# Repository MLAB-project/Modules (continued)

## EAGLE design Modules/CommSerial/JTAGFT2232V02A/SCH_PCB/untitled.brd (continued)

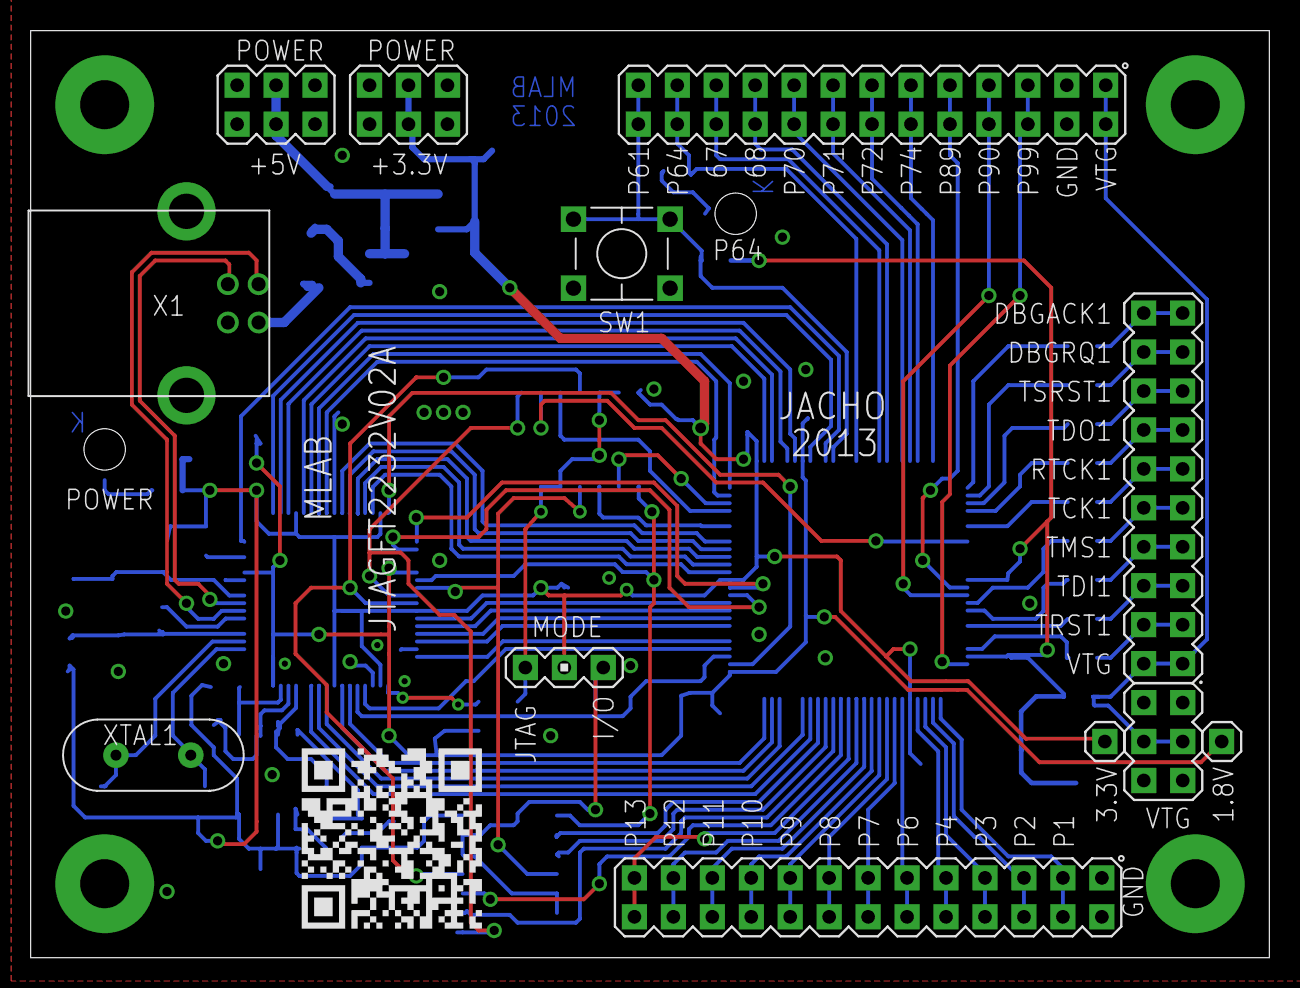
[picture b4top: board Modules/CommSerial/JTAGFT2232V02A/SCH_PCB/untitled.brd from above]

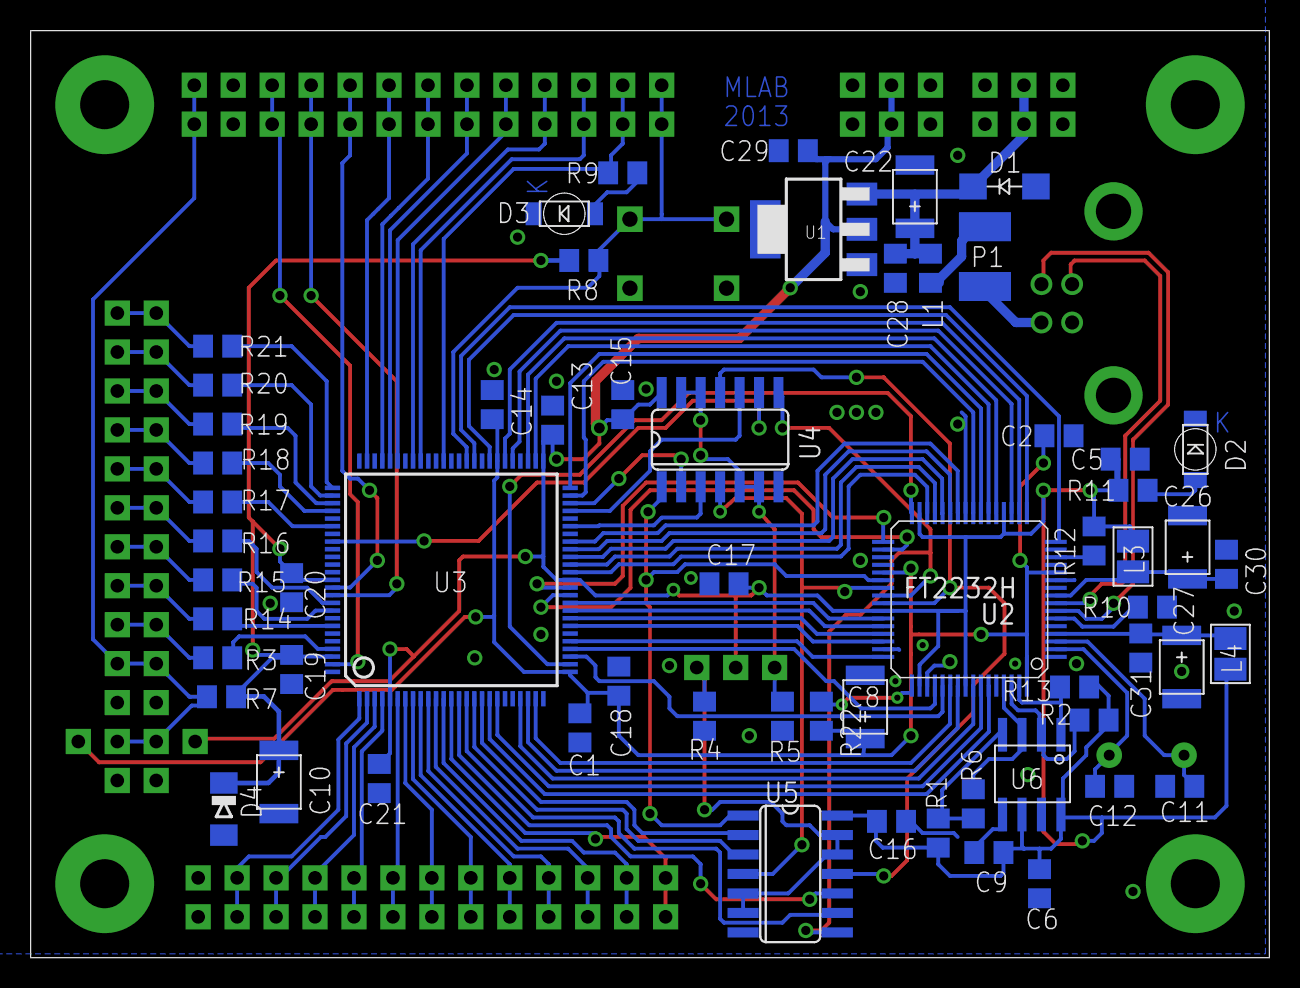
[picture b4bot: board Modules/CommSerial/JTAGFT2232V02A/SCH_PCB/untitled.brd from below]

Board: 2 copper layers, 80.8 x 60.5 mm, 77 parts (61 on the bottom side), 106 nets.

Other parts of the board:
SV9: MA01-1

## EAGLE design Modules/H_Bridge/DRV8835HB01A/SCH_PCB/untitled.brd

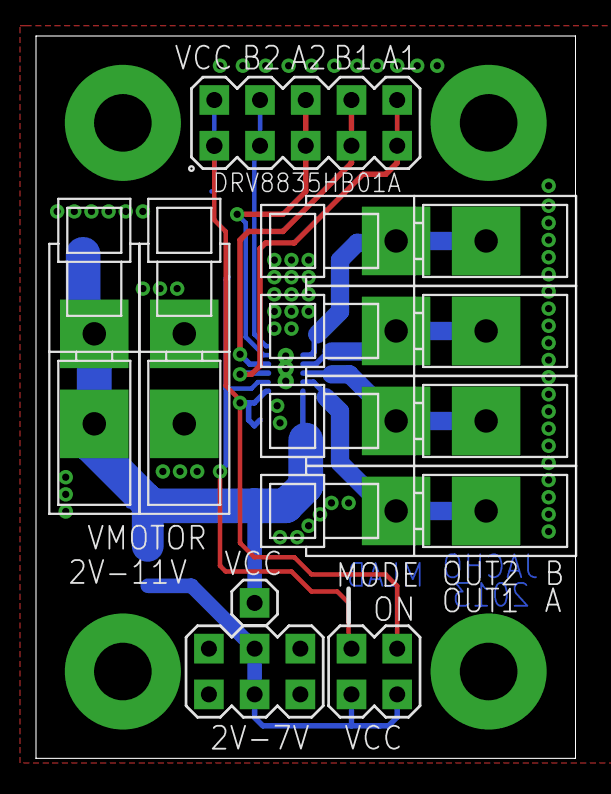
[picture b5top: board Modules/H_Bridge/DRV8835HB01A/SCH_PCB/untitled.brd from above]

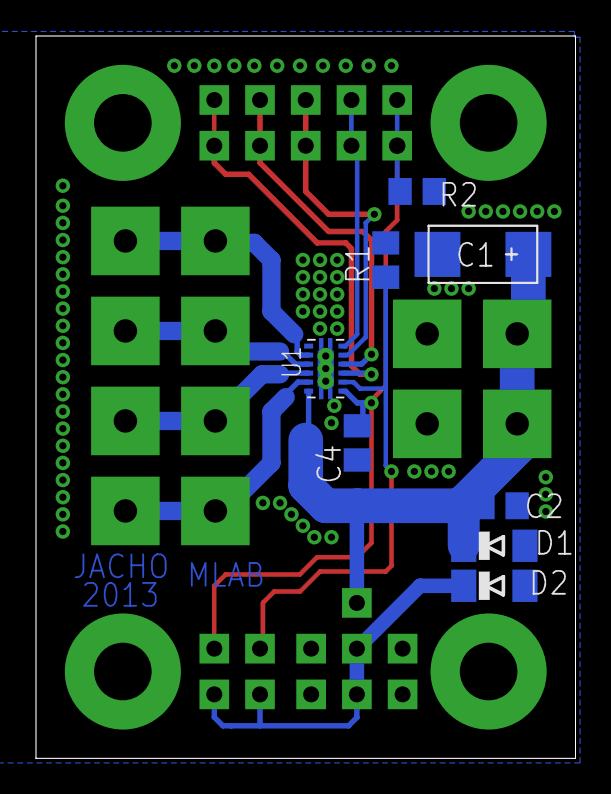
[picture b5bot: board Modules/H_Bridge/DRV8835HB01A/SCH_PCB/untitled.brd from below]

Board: 2 copper layers, 30.0 x 40.1 mm, 22 parts (8 on the bottom side), 13 nets.

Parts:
C1: C
C2: C0805
C4: 100nF; C0805
D1, D2: MINIMELF
R1, R2: 22k; 0805
SV1, SV2, SV3, SV4, SV7, SV8: WAGO256
SV5: MA05-2
SV6: MA02-2
SV9: MA03-2
SV10: MA01-1
U1: WSON
X1, X2, X3, X4: SROUB3M

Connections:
+VCC: D2.C, SV6.2, SV6.4, SV9.3, SV9.4
GND: C1.-, C2.2, C4.2, D1.A, D2.A, R1.1, R2.1, SV2.1, SV2.A1, SV9.1, SV9.2, SV9.5, SV9.6, U1.P1, U1.P2, U1.P3, U1.P4, U1.P5, U1.P6, U1.P7, U1.P8, U1.P$6, X1.P$1, X2.P$1, X3.P$1, X4.P$1
unnamed: SV5.5, SV5.6, U1.P$8
unnamed: SV5.3, SV5.4, U1.P$7
unnamed: R1.2, SV6.3, U1.P$11
unnamed: SV5.7, SV5.8, U1.P$9
unnamed: SV5.9, SV5.10, U1.P$10
unnamed: C4.1, R2.2, SV5.1, SV5.2, SV6.1, U1.P$12
unnamed: SV8.1, SV8.A1, U1.P$5
unnamed: SV7.1, SV7.A1, U1.P$4
unnamed: SV4.1, SV4.A1, U1.P$3
unnamed: SV3.1, SV3.A1, U1.P$2
VN: C1.+, C2.1, D1.C, SV1.1, SV1.A1, SV10.1, U1.P$1

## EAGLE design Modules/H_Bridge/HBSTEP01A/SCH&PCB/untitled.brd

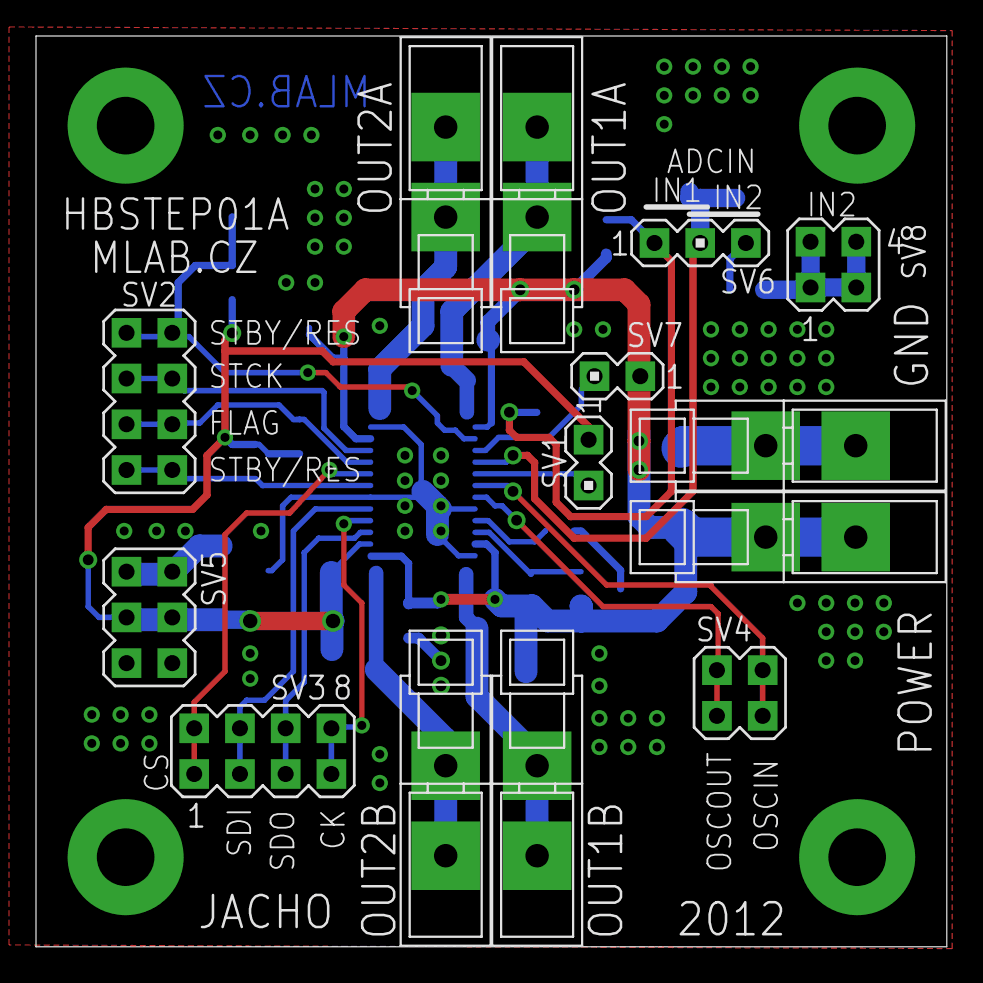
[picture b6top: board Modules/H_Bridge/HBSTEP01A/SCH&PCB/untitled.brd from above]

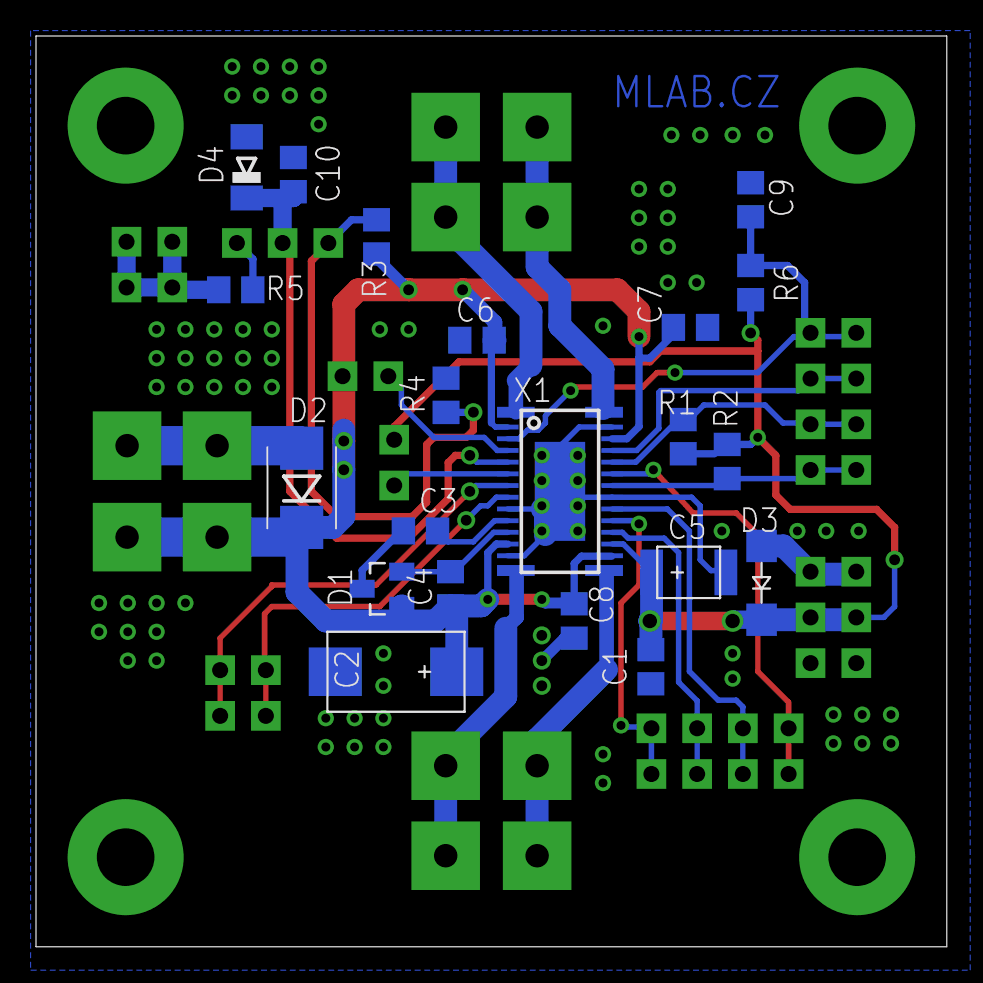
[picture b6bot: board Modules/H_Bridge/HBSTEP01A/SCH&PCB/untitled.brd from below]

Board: 2 copper layers, 50.6 x 50.6 mm, 39 parts (21 on the bottom side), 26 nets.

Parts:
C1: 100nF; C0805
C2: 22M/20V; D
C3: 10nF; C0805
C4: 220nF; C0805
C5: 10u/16V; B
C6, C7, C8: 100n; C0805
C9: 100p; C0805
C10: C0805
CON1, CON2, CON3, CON4, CON5, CON6: WAGO256
D1: BAT46SW; SOT23
D2: SMB
D3: M4; SMA
D4: MINIMELF
R1, R2, R4, R5, R6-PULLUP: 1K; R0805
R3: 68K; R0805
SV1, SV7: MA02-1
SV2: MA04-2
SV3: MA04-2@1
SV4: MA02-2
SV5: MA03-2
SV6: MA03-1
SV8: MA02-2@1
X1: HTSSOP28
X3, X4, X5, X6: SROUB3M

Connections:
+12V: C2.+, C4.1, C6.1, C7.1, C8.1, CON6.1, CON6.A1, D1.1, D2.K, R3.2, X1.2, X1.12, X1.16, X1.26
ADCIN: C10.1, D4.C, SV6.2, X1.5
GND: C1.2, C2.-, C5.-, C6.2, C7.2, C8.2, C9.2, C10.2, CON5.1, CON5.A1, D2.A, D3.A, D4.A, R4.1, SV5.1, SV5.2, SV5.5, SV5.6, SV7.1, X1.9, X1.13, X1.21, X1.27, X1.P$1, X3.P$1, X4.P$1, X5.P$1, X6.P$1
unnamed: R1.1, SV2.5, SV2.6, X1.24
unnamed: R2.1, SV2.7, SV2.8, X1.22
unnamed: SV2.3, SV2.4, X1.25
unnamed: C9.1, R6-PULLUP.1, SV2.1, SV2.2, X1.3
unnamed: SV3.1, SV3.2, X1.23
unnamed: SV3.3, SV3.4, X1.20
unnamed: SV3.5, SV3.6, X1.18
unnamed: SV1.2, X1.6
unnamed: SV7.2, X1.4
unnamed: SV4.3, SV4.4, X1.7
unnamed: CON4.1, CON4.A1, X1.28
unnamed: CON3.1, CON3.A1, X1.1
unnamed: CON1.1, CON1.A1, X1.14
unnamed: CON2.1, CON2.A1, X1.15
unnamed: SV4.1, SV4.2, X1.8
unnamed: SV3.7, SV3.8, X1.19
unnamed: R3.1, R4.2, SV6.1
unnamed: R5.2, SV6.3
unnamed: C4.2, D1.2, X1.11
unnamed: C3.2, D1.3
unnamed: C3.1, X1.10
unnamed: R5.1, SV8.1, SV8.2, SV8.3, SV8.4
VCC: C1.1, C5.+, D3.K, R1.2, R2.2, R6-PULLUP.2, SV1.1, SV5.3, SV5.4, X1.17

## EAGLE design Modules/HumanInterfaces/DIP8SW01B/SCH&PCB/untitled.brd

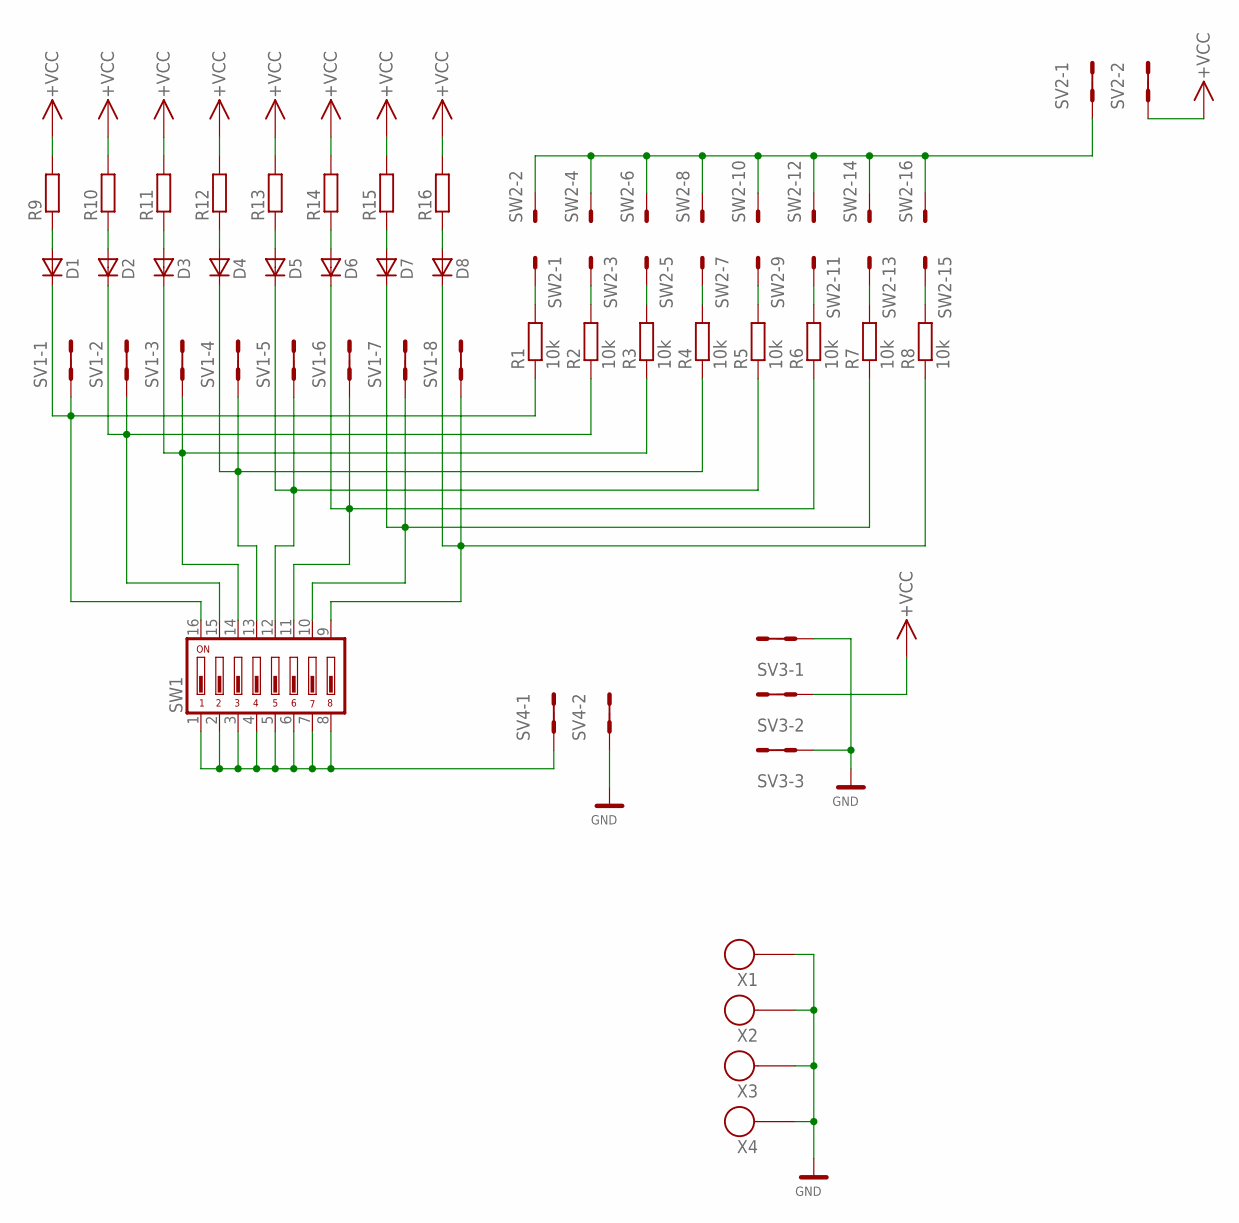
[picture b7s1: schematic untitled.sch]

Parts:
D1, D2, D3, D4, D5, D6, D7, D8: LED1206_2; 1206_2
R1, R2, R3, R4, R5, R6, R7, R8: 10k; 0805
R9, R10, R11, R12, R13, R14, R15, R16: R0805; 0805
SV1: MA08-2
SV2, SV4: MA02-2
SV3: MA03-2
SW1: DIP-08; DIP08SW
SW2: MA08-3; MA08-2
X1, X2, X3, X4: SROUB3M

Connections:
GND: SV3.1, SV3.2, SV3.5, SV3.6, SV4.3, SV4.4, X1.P$1, X2.P$1, X3.P$1, X4.P$1
unnamed: D1.K, R1.1, SV1.1, SV1.2, SW1.16
unnamed: D2.K, R2.1, SV1.3, SV1.4, SW1.15
unnamed: D3.K, R3.1, SV1.5, SV1.6, SW1.14
unnamed: D4.K, R4.1, SV1.7, SV1.8, SW1.13
unnamed: D5.K, R5.1, SV1.9, SV1.10, SW1.12
unnamed: D6.K, R6.1, SV1.11, SV1.12, SW1.11
unnamed: D7.K, R7.1, SV1.13, SV1.14, SW1.10
unnamed: D8.K, R8.1, SV1.15, SV1.16, SW1.9
unnamed: R1.2, SW2.1
unnamed: R2.2, SW2.3
unnamed: R3.2, SW2.5
unnamed: R4.2, SW2.7
unnamed: R5.2, SW2.9
unnamed: R6.2, SW2.11
unnamed: R7.2, SW2.13
unnamed: R8.2, SW2.15
unnamed: D2.A, R10.1
unnamed: D3.A, R11.1
unnamed: D4.A, R12.1
unnamed: SV2.1, SV2.2, SW2.2, SW2.4, SW2.6, SW2.8, SW2.10, SW2.12, SW2.14, SW2.16
unnamed: D5.A, R13.1
unnamed: SV4.1, SV4.2, SW1.1, SW1.2, SW1.3, SW1.4, SW1.5, SW1.6, SW1.7, SW1.8
unnamed: D6.A, R14.1
unnamed: D7.A, R15.1
unnamed: D1.A, R9.1
unnamed: D8.A, R16.1
VCC: R9.2, R10.2, R11.2, R12.2, R13.2, R14.2, R15.2, R16.2, SV2.3, SV2.4, SV3.3, SV3.4

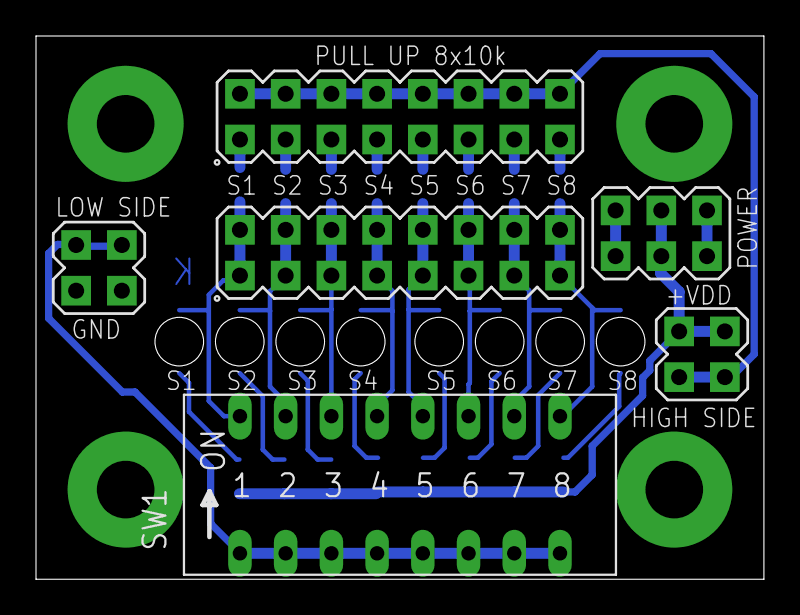
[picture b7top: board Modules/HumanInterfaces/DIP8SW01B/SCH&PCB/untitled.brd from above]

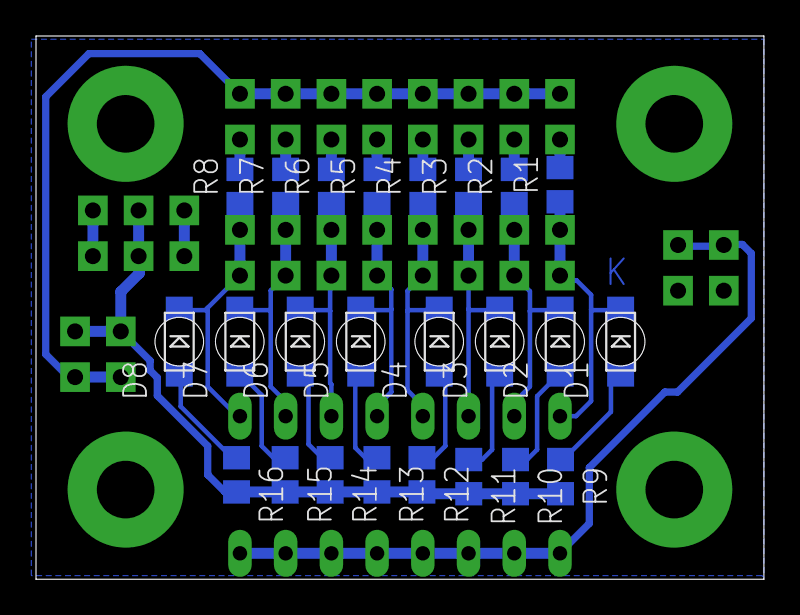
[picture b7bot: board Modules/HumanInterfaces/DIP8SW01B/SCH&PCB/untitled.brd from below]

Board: 2 copper layers, 40.4 x 30.2 mm, 34 parts (24 on the bottom side), 28 nets.
